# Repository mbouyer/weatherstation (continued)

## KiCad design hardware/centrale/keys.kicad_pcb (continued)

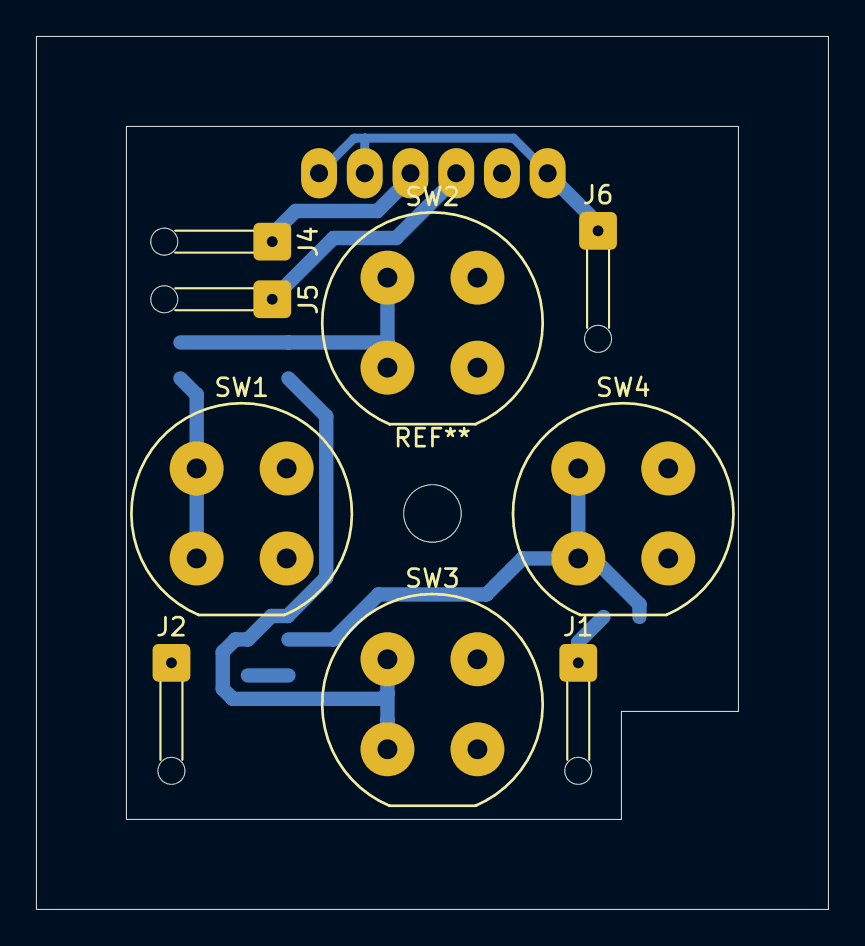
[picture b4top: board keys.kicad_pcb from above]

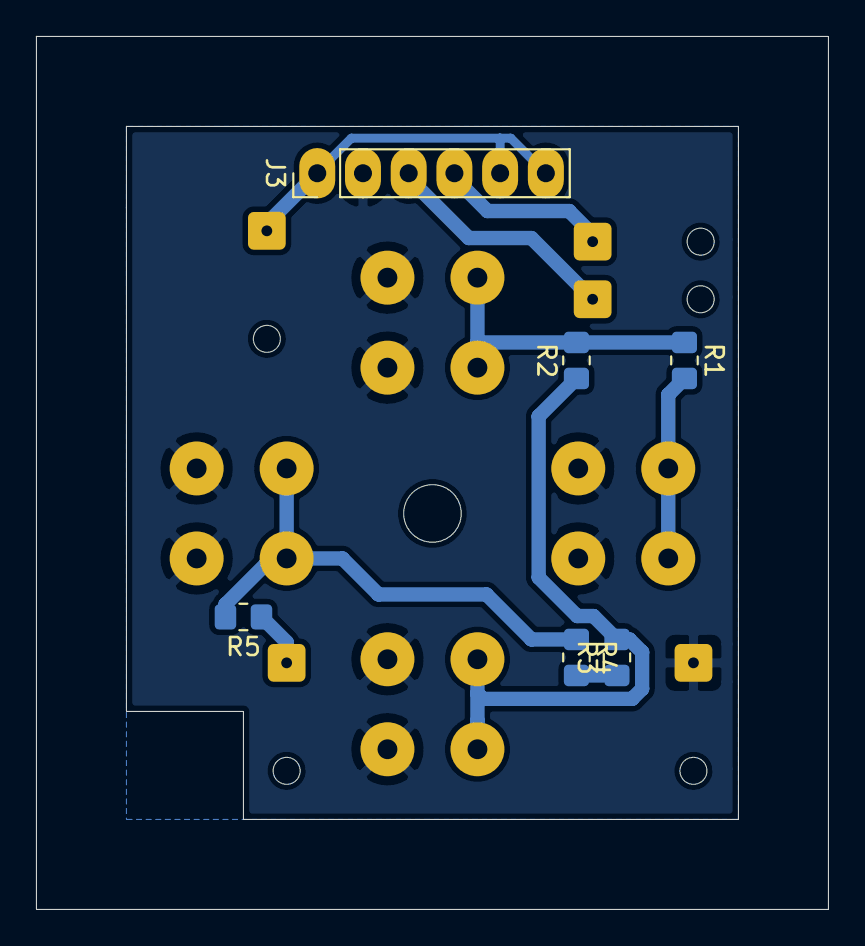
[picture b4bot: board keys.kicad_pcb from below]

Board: 2 copper layers, 44.0 x 48.5 mm, 15 parts (6 on the bottom side), 10 nets.

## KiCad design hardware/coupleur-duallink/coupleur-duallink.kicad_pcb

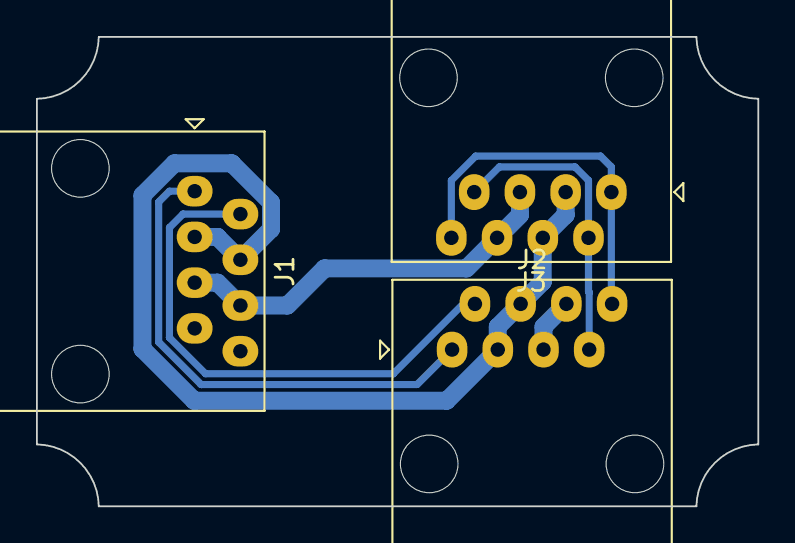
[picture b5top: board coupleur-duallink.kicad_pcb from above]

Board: 2 copper layers, 40.1 x 26.1 mm, 3 parts (0 on the bottom side), 6 nets.

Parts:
J1, J2, J3: RJ45; RJ45_Amphenol_54602-x08_Horizontal

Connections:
/+12V: J1.3, J1.4, J2.3, J2.4, J3.3, J3.4
/GND: J1.5, J1.6, J2.5, J2.6, J3.5, J3.6
unnamed: J1.1, J2.1
unnamed: J1.2, J2.2
unnamed: J2.7, J3.2, J3.7
unnamed: J2.8, J3.1, J3.8

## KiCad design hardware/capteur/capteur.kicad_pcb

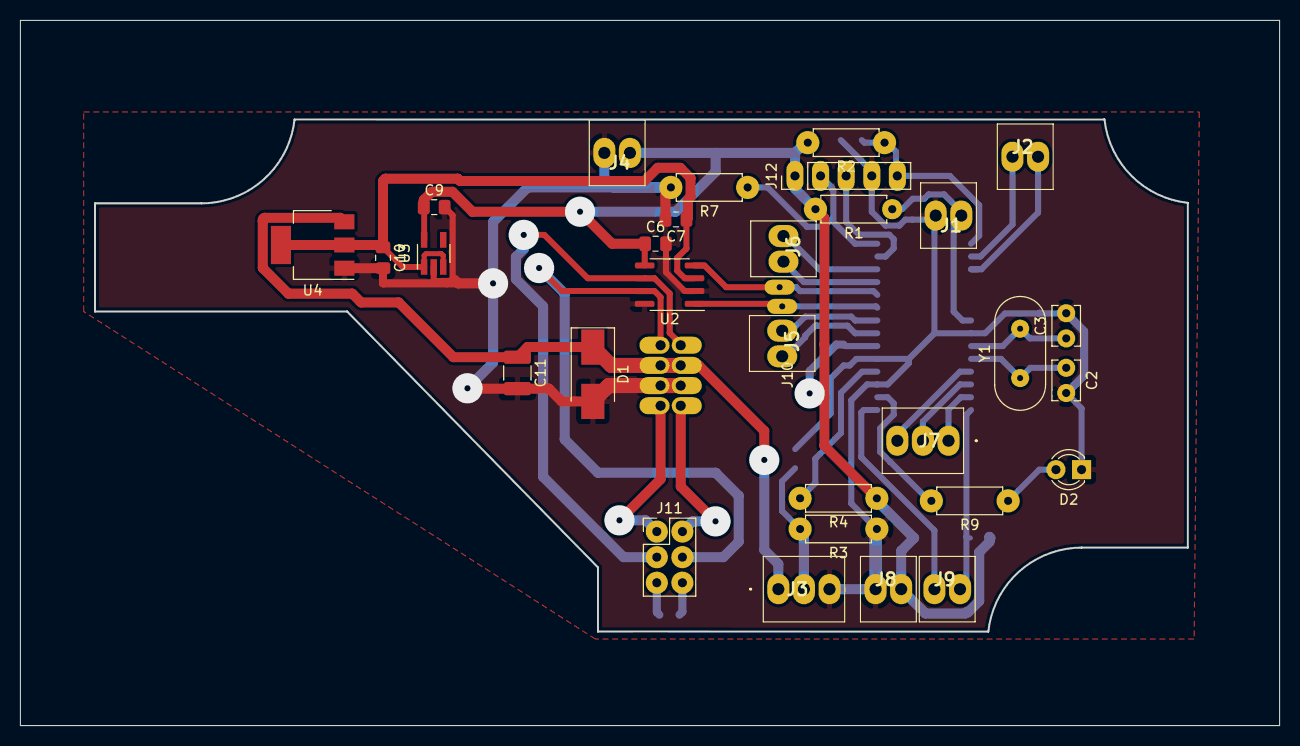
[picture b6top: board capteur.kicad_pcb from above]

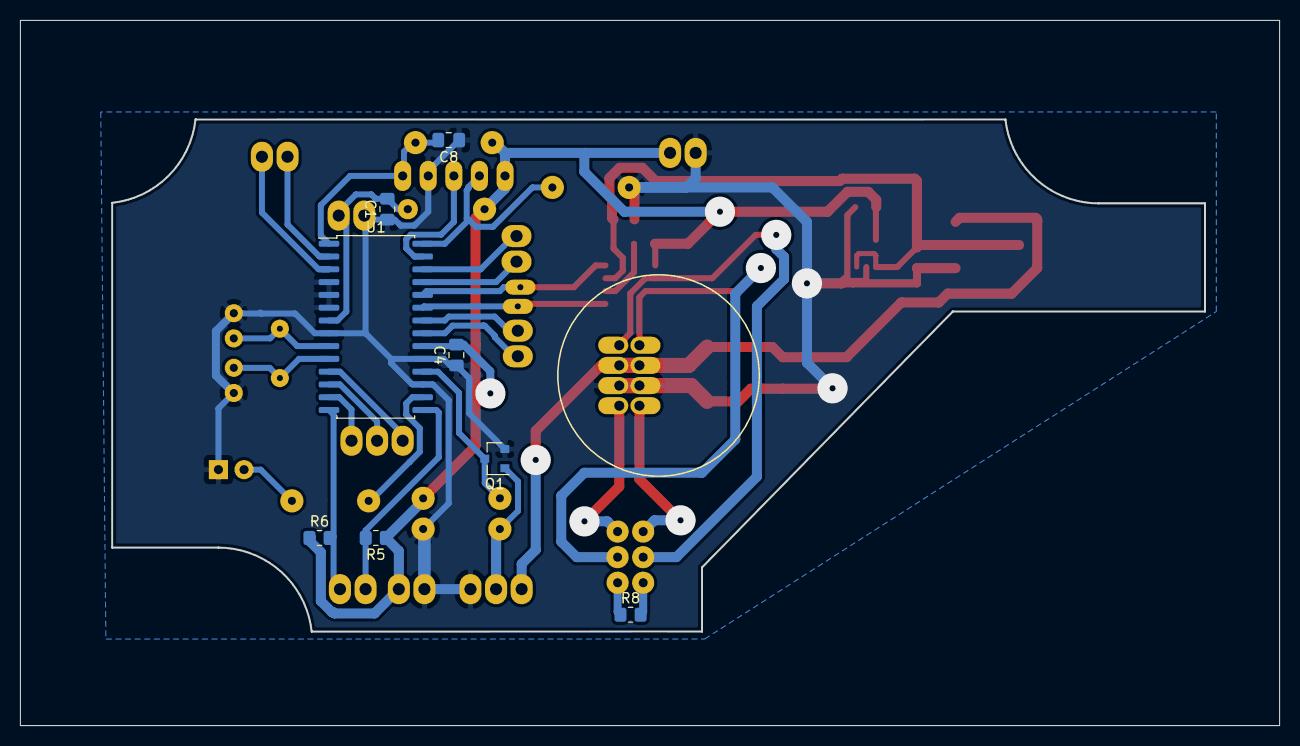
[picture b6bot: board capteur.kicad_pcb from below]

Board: 2 copper layers, 124.9 x 69.9 mm, 39 parts (8 on the bottom side), 33 nets.

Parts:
C1, C4, C6, C7, C8: 100nF; C_0805_2012Metric_Pad1.18x1.45mm_HandSolder
C2, C3: 22pF; C_Disc_D3.8mm_W2.6mm_P2.50mm
C9, C10: 1uF; C_0805_2012Metric_Pad1.18x1.45mm_HandSolder
C11: 10uF; C_1210_3225Metric_Pad1.33x2.70mm_HandSolder
D1: SMBJ16A; D_SMB_Handsoldering
D2: RED; LED_D3.0mm
J1: Pluvio; 282834-2_1
J2, J4, J5, J6: Conn_01x02_Male; 282834-2_1
J3: NMEA0183 (wind); 282834-3
J7: Conn_01x03_Male; 282834-3
J8: STH20 pwr; 282834-2_1
J9: STH20 i2c; 282834-2_1
J10: RJ45; multicomp_MP002453-swappedpins
J11: Term_sel; PinHeader_2x03_P2.54mm_Vertical
J12: Conn_01x05_Male; PinHeader_1x05_P2.54mm_Vertical
Q1: NMOS; SOT-23
R1, R2, R3, R7: 10K; R_Axial_DIN0207_L6.3mm_D2.5mm_P7.62mm_Horizontal
R4: 1K; R_Axial_DIN0207_L6.3mm_D2.5mm_P7.62mm_Horizontal
R5, R6: 4K7; R_0805_2012Metric_Pad1.20x1.40mm_HandSolder
R8: 100; R_0805_2012Metric_Pad1.20x1.40mm_HandSolder
R9: 330; R_Axial_DIN0207_L6.3mm_D2.5mm_P7.62mm_Horizontal
U1: PIC18F27Q84_ISS; SOIC-28W_7.5x17.9mm_P1.27mm
U2: TLE9250VSJXUMA1; SOIC-8_3.9x4.9mm_P1.27mm
U3: mic5504-3.3; SOT-23-5_HandSoldering
U4: LDL1117S50; SOT-223-3_TabPin2
Y1: 10Mhz; Crystal_HC18-U_Vertical

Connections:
+3V3: C4.2, C6.1, C9.1, J4.1, J8.2, J12.1, R1.2, R2.2, R4.1, R5.1, R6.1, U1.20, U2.5, U3.5
+5V: C7.1, C10.1, U2.3, U3.1, U3.3, U4.2
+12V: C11.1, D1.1, J3.1, J10.3, J10.4, U4.3
/CANH: J10.1, J11.4, U2.7
/CANL: J10.2, J11.3, U2.6
/CANRX: U1.24, U2.4
/CANTX: U1.23, U2.1
/MCLR: C8.2, J12.5, R2.1, U1.1
/PGC: J12.3, U1.27
/PGD: J12.2, R7.1, U1.28
/SCL: J9.2, R6.2, U1.14
/SDA: J9.1, R5.2, U1.15
GND: C1.1, C2.2, C3.2, C4.1, C6.2, C7.2, C8.1, C9.2, C10.2, C11.2, D1.2, D2.1, J1.2, J3.3, J4.2, J8.1, J10.5, J10.6, J12.4, Q1.2, R3.1, R7.2, U1.4, U1.5, U1.6, U1.8, U1.17, U1.19, U2.2, U2.8, U3.2, U4.1
unnamed: C1.2, J1.1, R1.1, U1.7
unnamed: C2.1, U1.10, Y1.1
unnamed: C3.1, U1.9, Y1.2
unnamed: D2.2, R9.1
unnamed: J2.1, U1.2
unnamed: J2.2, U1.3
unnamed: J3.2, Q1.1, R3.2
unnamed: J5.1, U1.22
unnamed: J5.2, U1.21
unnamed: J6.1, U1.26
unnamed: J6.2, U1.25
unnamed: J7.1, U1.13
unnamed: J7.2, U1.12
unnamed: J7.3, U1.11
unnamed: J10.7, J11.1
unnamed: J10.8, J11.2
unnamed: J11.5, R8.2
unnamed: J11.6, R8.1
unnamed: Q1.3, R4.2, U1.18
unnamed: R9.2, U1.16

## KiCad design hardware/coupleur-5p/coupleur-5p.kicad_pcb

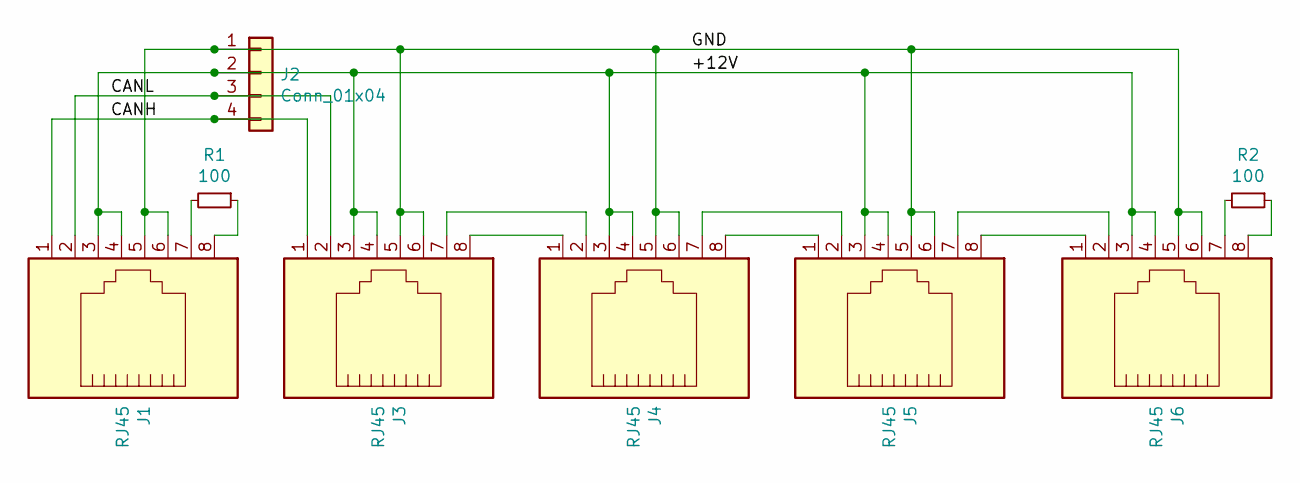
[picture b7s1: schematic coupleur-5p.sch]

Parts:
J1, J3, J4, J5, J6: RJ45; RJ45_Amphenol_54602-x08_Horizontal
J2: Conn_01x04; PinHeader_1x04_P2.54mm_Vertical
R1, R2: 100; R_0805_2012Metric_Pad1.20x1.40mm_HandSolder

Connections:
/+12V: J1.3, J1.4, J2.2, J3.3, J3.4, J4.3, J4.4, J5.3, J5.4, J6.3, J6.4
/CANH: J1.1, J2.4, J3.1
/CANL: J1.2, J2.3, J3.2
/GND: J1.5, J1.6, J2.1, J3.5, J3.6, J4.5, J4.6, J5.5, J5.6, J6.5, J6.6
unnamed: J1.7, R1.2
unnamed: J1.8, R1.1
unnamed: J3.7, J4.2
unnamed: J3.8, J4.1
unnamed: J4.7, J5.2
unnamed: J4.8, J5.1
unnamed: J5.7, J6.2
unnamed: J5.8, J6.1
unnamed: J6.7, R2.2
unnamed: J6.8, R2.1

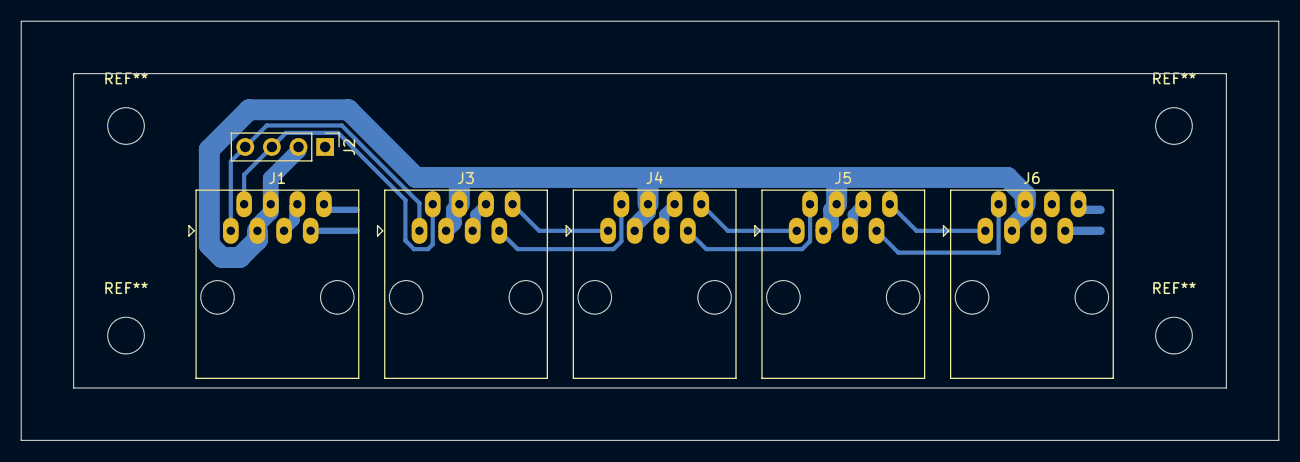
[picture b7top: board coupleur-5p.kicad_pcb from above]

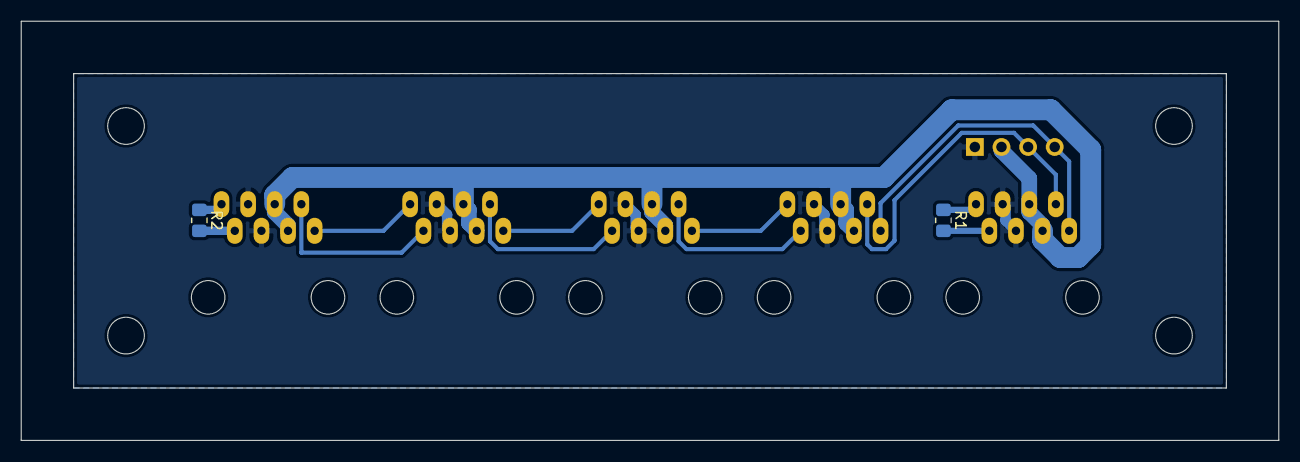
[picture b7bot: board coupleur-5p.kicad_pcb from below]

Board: 2 copper layers, 120.0 x 40.0 mm, 8 parts (2 on the bottom side), 14 nets.

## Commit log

2021-04-18 Image de l'afficheur Vetus
2021-04-18 Commit initial du projet
2021-04-23 Modifications mineures pour fabrication
2021-04-23 L'empreinte utilisée pour le connecteur RJ45 MP002453 est inversée; modification du nom utilisé pour le montrer.
2021-04-24 Configuration kernel et device tree pour netbsd-9.
2021-04-26 Disable more devices. Especially AHCI which shares a pin with LCD_RSTB
2021-04-26 firmware de base pour les pic18, avec support CAN/N2K. Ils obtiennent une adresse et répondent au message ISO_ADDRESS_CLAIM
2021-04-26 s/power/vetus/g
2021-04-26 Marque NMEA2000_USER_DEVICE_CLASS explicitement comme unsigned, pour éviter un overflow dans la lib N2K
2021-04-26 s/power/capteur/g
2021-04-26 Marque NMEA2000_USER_DEVICE_CLASS comme unsigned pour éviter un overflow dans le code N2K
2021-04-26 Rends la convertion .hex -> .bin optionelle, la programmation a travers le bus CAN utilise le .hex
2021-04-26 Surpression de NMEA2000_USER_NAME, non-utilisé
2021-04-26 Initialise I2C et le DAC MCP4706.
2021-04-27 Correction adresse vecteurs.
2021-04-27 define CAN_PORTB (après MAJ de pic18_n2k)
2021-04-27 Configure les LEDs et BATT_ON
2021-04-28 Add i2c infrastructure and read the INA226 manuf/die code.
2021-04-28 Query and send periodic battery status
2021-04-28 Setup and use the ADCC to query the input voltage
2021-04-30 Configuration su ina226 pour ~1mesure/s
2021-04-30 Supression de l'utilisation de INA_ALERT: nous n'utiliseront pas les alertes et le bit CONVERTION_READY n'est pas utilisable en mode continous. is not set in continous mode.
2021-04-30 Mesure la NTC (température de la batterie)
2021-04-30 Send DC_DETAILED_STATUS PGN.
2021-04-30 Correction de l'arrondi dans NMEA2000_DC_STATUS
2021-04-30 define NEMA2000_USE_FAST_FRAME
2021-04-30 Implementation du chargeur. Le calcul de l'état de charge est basique.
2021-04-30 Corrige débordement dans le calcul du SoC
2021-04-30 Don't forget TRISB1 (CHRG)
2021-05-01 Cleanup softintrs
2021-05-01 Lecture température/humidité du STH20
2021-05-01 Transmet les trames NMEA2000_ENV_PARAM
2021-05-01 Nome les signaux SCL et SDA (pour repérage facile)
2021-05-01 Configure timer1 pour compter les impulsions du pluviomètre
2021-05-02 utilise des #define pour les constantes batteries. Pas de changement fonctionnel
2021-05-03 Premier jet du support batterie/PCB pour l'alimentation. Prévu pour un boitier DN16E
2021-05-03 Prévois 1mm de jeu en bas du PCB. Ajustements pour l'utilisation d'inserts M3
2021-05-03 Fichier dupliqué
2021-05-03 Fichier dupliqués dans CAD/
2021-05-03 Découpe pour les connecteurs dans le boitier.
2021-05-04 Ajout de butées pour maintenir la batterie centrée.
2021-05-04 trace les butées sur une couche différente
2021-05-04 Réhausse les butées.
2021-05-05 Ajout référence NTC
2021-05-05 Correction des valeurs d'après la datasheet de la thermistance
2021-05-05 Correction problème signed/unsigned
2021-05-05 Configure le port série pour la réception NMEA
2021-05-05 Parse NMEA1083 WMV and send NMEA2000_WIND_DATA
2021-05-05 Envoi de PRIVATE_RAIN_COUNTER, et diverses petite corrections
2021-05-06 Autotest de l'affichage au boot, timeout sur les données de vent
2021-05-06 créé une fonction pour la gestion des LEDs. Implémente la réception des trames WIND_DATA
2021-05-07 Modifs pour l'usinage
2021-05-08 Ajustement de la convertion vent/DAC
2021-05-23 Debut d'un driver CAN/N2k pour weewx. Gère NMEA2000_ENV_PARAM et PRIVATE_RAIN_COUNTER pour le moment.
2021-05-23 Ajout NMEA2000_WIND_DATA
2021-05-24 Un service pour weewx, qui ajoutes les données issues de la commande envstat pour la télémetrie
2021-05-26 Abaisse le taux de donnnées vent à max un par seconde, en calculant et envoyant la moyenne sur l'intervalle. Un taux de messages trop élevé est trop gourmand en CPU avec MQTT
2021-05-29 renvoie une erreur en cas de timeout dans I2C_WAIT au lieu de faire un reset. Rend le capteur plus robuste en cas de défaillance de la sonde SHT20
2021-05-30 Add PGN 127508 (NMEA2000_BATTERY_STATUS)
2021-05-30 Ajoute la correction du décalage dans la direction du vent
2021-05-31 Add extra data sets to weewx.units
2021-06-03 La doc dit: mettre à zero les deux bits de poids faible avant de calculer les valeurs température et humidité.
2021-06-03 Limite les valeurs d'humidité à [0-100]
2021-10-17 Prepare for v2: fix display connector wiring, remplace the CAN transeiver with a pin-compatible one which is not out of stock, enlarge a bit the CPU cooling window.
2021-10-17 Use a MC24356 connector for the CPU power supply. Other minor cleanups
2021-10-17 Add a simple command line program to dump the power battery status
2021-10-18 Add a coupler using both CAN link (for rescue of broken connector)
2021-10-20 Change DC/DC output capacitors to 1210 size. Theses are better at 5V bias, hoping this will decrease the noise of the inductor.
2021-10-31 Adjust ANEMO_DIR_OFFSET
2022-01-12 More clearance
2022-01-29 Adjust for pic18_n2k changes
2022-03-15 capteur: Update schematic for v2 switch to pic18f27q84, change CAN transeiver reference (it's pin-compatible), switch regulators to LDL1117S50/mic5504-3.3. Also use a RJ45 connector with the right pi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
2022-03-15 capteur v2: shrink PCB by 0.5mm on all edges, so that it fits better in enclosure. remove mounting hole, we don't use them.
2022-03-15 capteur v2: add a LED for debug purposes.
2022-03-16 On second though, keep the swappedpin connector - we already have the cable :)
2022-03-16 Swap crystal pins to match PCB
2022-03-16 Connect pic18's unused pins to GND
2022-03-16 Increase isolation to 0,3mm reroute PCB after schematic changes.
2022-03-24 Enlarge some through-hole pad, for easier soldering
2022-03-27 Convert back more pads to via. Move vias outside of component footprint
2022-03-28 Add a 5-connectors coupler, for a star-like wiring.
2022-03-30 Remove local-only files
2022-03-30 Remove more local-only files
2022-03-30 Add a small PCB for 4 buttons and a BME280 module.
2022-03-30 Begin designing an enclosure
2022-03-30 Add back cleaned up local libraries configuration
2022-03-30 Adjust some dimensions Add some informations
2022-03-30 First version of PCB support.
2022-03-31 Generate gerber files for new capteur version
2022-03-31 Longer holes for PCB screws
2022-03-31 WIP on display emclosure
2022-03-31 more space for clips
2022-03-31 Add PCB supports
2022-03-31 Add supports for the LCD
2022-03-31 - Round the harms - mirror the whole thing, as the Z axis ix reversed
2022-03-31 Adjust holes for our M3 inserts
2022-03-31 Add hole for screws on arms
2022-04-01 Add 5mm margin around PCBs
2022-04-01 Fix edges; only 2 layers
2022-04-01 Only 2 layers
2022-04-01 Add some fabrication files
2022-04-02 better shape for clips
2022-04-05 clips are not strong enough, so remplace with a screw for PCB
2022-04-06 Regen fab files
2022-04-07 For next time: add a missing wire on LRADC
2022-04-07 Generate pcb support fab file
2022-04-07 Add real dimensions from printed PCB support.
2022-04-11 Update for V2 hardware, pic18f27q84-based
2022-04-12 Shrink a bit the base, to make sure it fits in the other part
2022-04-12 Better LCD support
2022-04-12 Add lcd locks
2022-04-13 Generate STL fle for LCD support
2022-04-13 Add lock clips STL
2022-04-14 Ajust locks with real sizes
2022-04-15 Sync dts with hardware reality
2022-04-15 WIP on a littlevg aplication for the LCD. It also gets data from the BME280 and push them to the CAN bus
2022-04-16 Fix SHT20 address (we want the R/W bit inclued now) Make sure RA5 is input
2022-04-16 Fix pressure/barometer input (we don't strictly follow n2k here to have better resolution)
2022-05-02 Fix connectors mounting holes
2023-02-19 Need <cstdlib> for newer gcc
2023-02-19 display time on bottom right of main page
2023-03-14 update capteur & centrale to new kicad format
2023-03-14 Convert power and vetus to new kicad format
2023-04-15 Name CANH and CANL nets
2024-07-21 Implement N2K_PRINTF Ignore wind data with overflow Ignore wind data with bad checksums For some reason we get framing errors, and the bit doesn't reset as expected so ignore framing errors
2025-04-21 Adjust capteur wind offset
